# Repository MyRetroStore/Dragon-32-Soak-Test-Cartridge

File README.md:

# Dragon 32 Soak Test Cartridge

From the description on [WorldOfDragon](https://archive.worldofdragon.org/index.php?title=Dragon_32_Soak_Test)

_A cartridge designed to test the Dragon 32 hardware in a loop.
The ROM program will change a pattern on screen and lit a green led on the cartridge if tests are passing, and freeze the machine and lit a red led if any test fails.
The cartridge will not work on a Dragon 64 or a Dragon 200 as it performs a ROM checksum and later models will make the checksum test fail._

There is not much documentation on the Soak Test Cartridge for the Dragon 32 computer. 

After finding a photo of the PCB on WorldOfDragon I decided to reverse engineer the PCB 
and with the help of the community on the forums as well as a Dragon 32 Facebook group, I've managed to re-create the schematic and a replica PCB.

## Folders
Hardware - Schematic, PCB layout and Gerbers created with [KiCad](https://www.kicad.org/) 7.0.10

ROM - Binary file from worldofdragon.org

Photos - Photos of the orignal and replica PCB as well as screenshots of the cartridge in action. 

## BOM

| Reference  | Component                           |
| ---------- | ----------------------------------- |
| C1	       | 10u Electrolytic Capacitor          |
| C2,C3      | 10n Ceramic Capacitor               |
| D1	       | Red 5mm LED                         |
| D2	       | Green 5mm LED                       |
| DC1-4	     | 100n Ceramic Capacitor (Decoupling) |
| IC1	       | 74LS04                              |
| IC2	       | LM555                               |
| IC3	       | EPROM 27C64                         |
| IC4	       | 74LS10                              |
| R1-2, R5-8 | 3k3 Resistor 0.25W                  |
| R3         | 100k Resistor 0.25W                 |
| R4	       | 1k Resistor 0.25W                   |
| TR1,TR2    | BC237 Transistor                    |

I've tested the PCB in my Dragon 32 and it seems to work as expected, however I do not take any responsibility if you are building this and there is damage done to your Dragon 32 due to incorrect assembly or it doesn't work as expected. 

While this should be as close as possible a 100% replica to the orignal PCB there could be some error (Though hopefully not. Let me know if you find any) 

## Purchasing

If you don't want build this yourself the completed PCB can be purchased from:
- [MyRetroStore](https://myretrostore.co.uk/)
- [eBay](https://www.ebay.co.uk/str/myretrostoreuk)

## License
GNU General Public License v3.0

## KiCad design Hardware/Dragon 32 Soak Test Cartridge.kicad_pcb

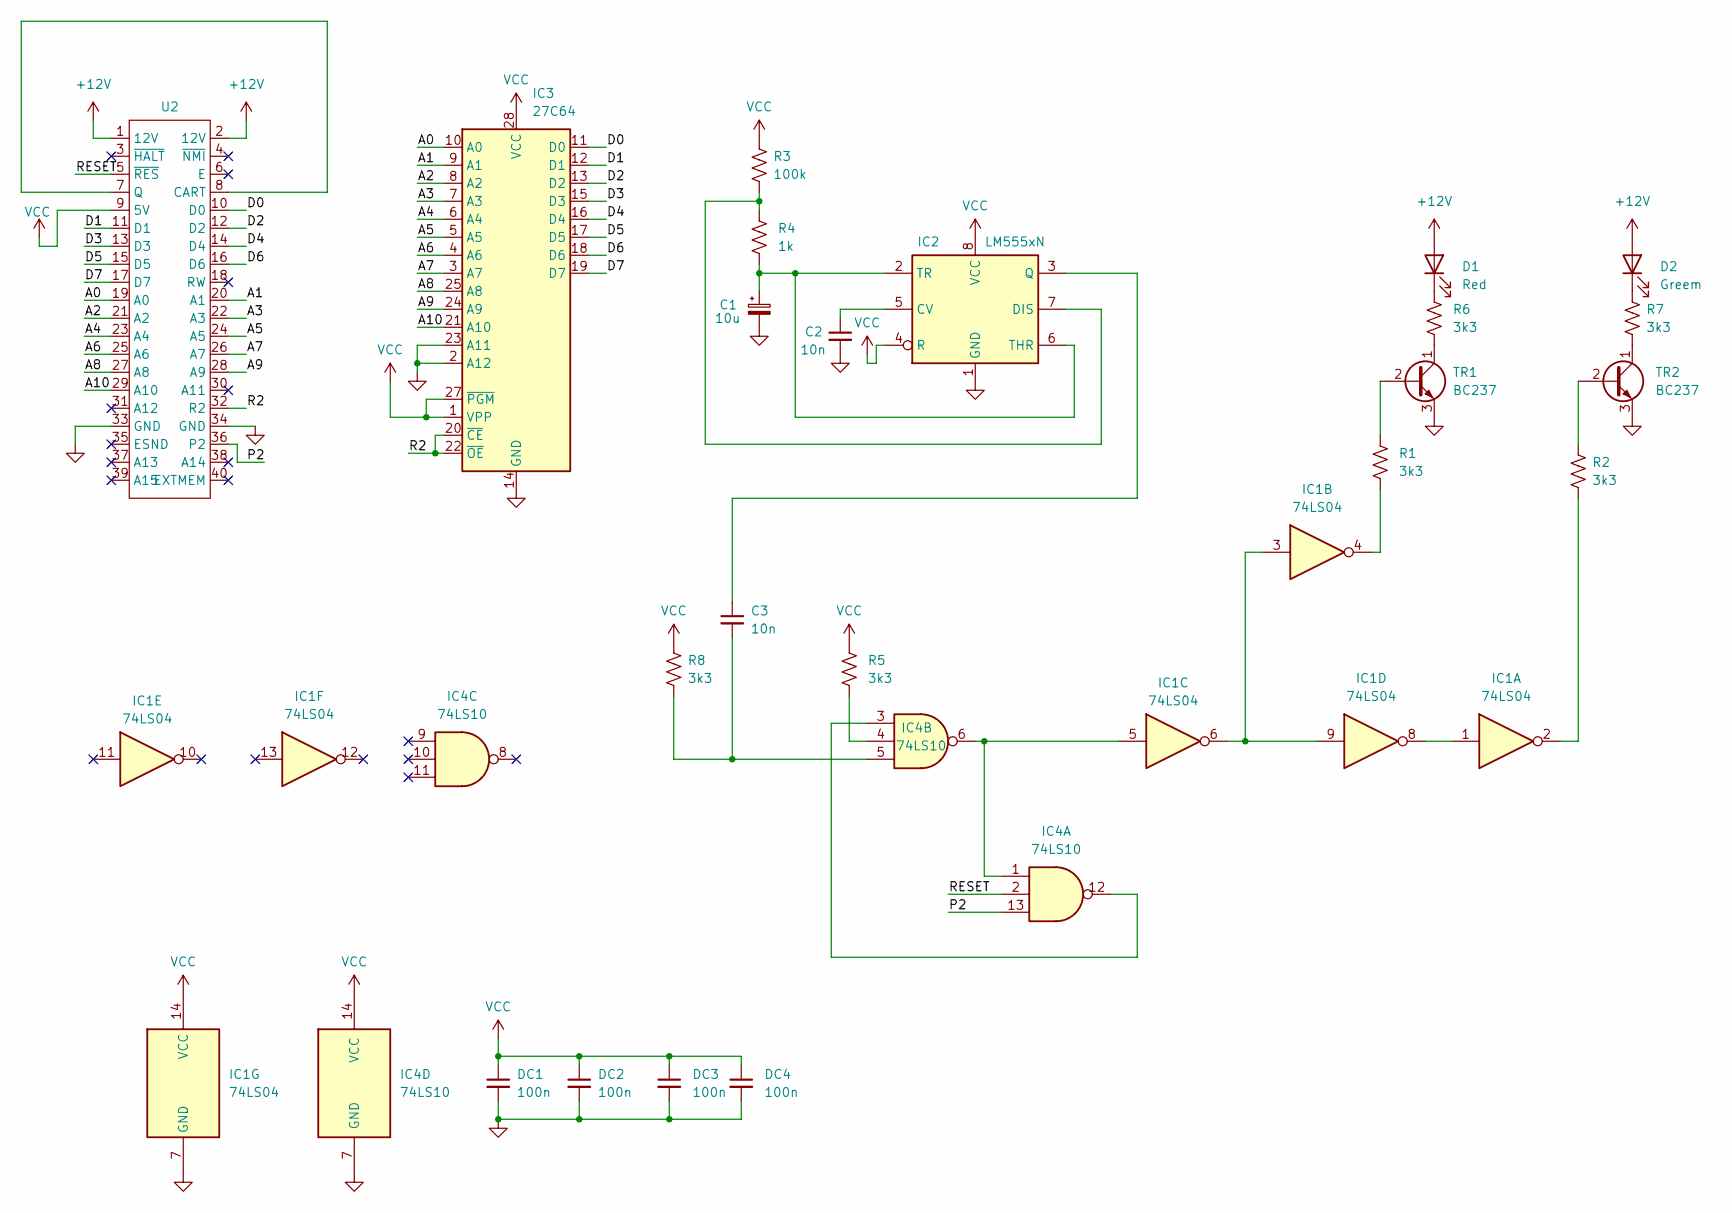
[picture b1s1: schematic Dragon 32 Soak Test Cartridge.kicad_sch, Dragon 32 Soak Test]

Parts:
C1: 10u; CP_Radial_D5.0mm_P2.50mm
C2, C3: 10n; C_Disc_D5.0mm_W2.5mm_P5.00mm
D1: Red; LED_D5.0mm
D2: Greem; LED_D5.0mm
DC1, DC2, DC3, DC4: 100n; C_Disc_D5.0mm_W2.5mm_P5.00mm
IC1: 74LS04; DIP-14_W7.62mm
IC2: LM555xN; DIP-8_W7.62mm
IC3: 27C64; DIP-28_W15.24mm
IC4: 74LS10; DIP-14_W7.62mm
R1, R2, R5, R6, R7, R8: 3k3; R_Axial_DIN0207_L6.3mm_D2.5mm_P10.16mm_Horizontal
R3: 100k; R_Axial_DIN0207_L6.3mm_D2.5mm_P10.16mm_Horizontal
R4: 1k; R_Axial_DIN0207_L6.3mm_D2.5mm_P10.16mm_Horizontal
TR1, TR2: BC237; TO-92
U2: Dragon 32

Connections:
+12V: D1.2 (A), D2.2 (A), U2.1 (12V), U2.2 (12V)
/A0: IC3.10 (A0), U2.19 (A0)
/A1: IC3.9 (A1), U2.20 (A1)
/A2: IC3.8 (A2), U2.21 (A2)
/A3: IC3.7 (A3), U2.22 (A3)
/A4: IC3.6 (A4), U2.23 (A4)
/A5: IC3.5 (A5), U2.24 (A5)
/A6: IC3.4 (A6), U2.25 (A6)
/A7: IC3.3 (A7), U2.26 (A7)
/A8: IC3.25 (A8), U2.27 (A8)
/A9: IC3.24 (A9), U2.28 (A9)
/A10: IC3.21 (A10), U2.29 (A10)
/D0: IC3.11 (D0), U2.10 (D0)
/D1: IC3.12 (D1), U2.11 (D1)
/D2: IC3.13 (D2), U2.12 (D2)
/D3: IC3.15 (D3), U2.13 (D3)
/D4: IC3.16 (D4), U2.14 (D4)
/D5: IC3.17 (D5), U2.15 (D5)
/D6: IC3.18 (D6), U2.16 (D6)
/D7: IC3.19 (D7), U2.17 (D7)
/P2: IC4.13, U2.36 (P2)
/R2: IC3.20 (~CE), IC3.22 (~OE), U2.32 (R2)
/RESET: IC4.2, U2.5 (~RES)
GND: C1.2, C2.2, DC1.2, DC2.2, DC3.2, DC4.2, IC1.7 (GND), IC2.1 (GND), IC3.2 (A12), IC3.14 (GND), IC3.23 (A11), IC4.7 (GND), TR1.3 (E), TR2.3 (E), U2.33 (GND), U2.34 (GND)
unnamed: C3.2, IC4.5, R8.1
unnamed: D1.1 (K), R6.1
unnamed: D2.1 (K), R7.1
unnamed: IC1.1, IC1.8
unnamed: IC1.2, R2.2
unnamed: IC1.3, IC1.6, IC1.9
unnamed: IC1.4, R1.2
unnamed: IC1.5, IC4.1, IC4.6
unnamed: C2.1, IC2.5 (CV)
unnamed: IC2.7 (DIS), R3.1, R4.1
unnamed: C3.1, IC2.3 (Q)
unnamed: C1.1, IC2.2 (TR), IC2.6 (THR), R4.2
unnamed: IC4.4, R5.2
unnamed: IC4.3, IC4.12
unnamed: R1.1, TR1.2 (B)
unnamed: R6.2, TR1.1 (C)
unnamed: R2.1, TR2.2 (B)
unnamed: R7.2, TR2.1 (C)
unnamed: U2.7 (Q), U2.8 (CART)
VCC: DC1.1, DC2.1, DC3.1, DC4.1, IC1.14 (VCC), IC2.4 (R), IC2.8 (VCC), IC3.1 (VPP), IC3.27 (~PGM), IC3.28 (VCC), IC4.14 (VCC), R3.2, R5.1, R8.2, U2.9 (5V)

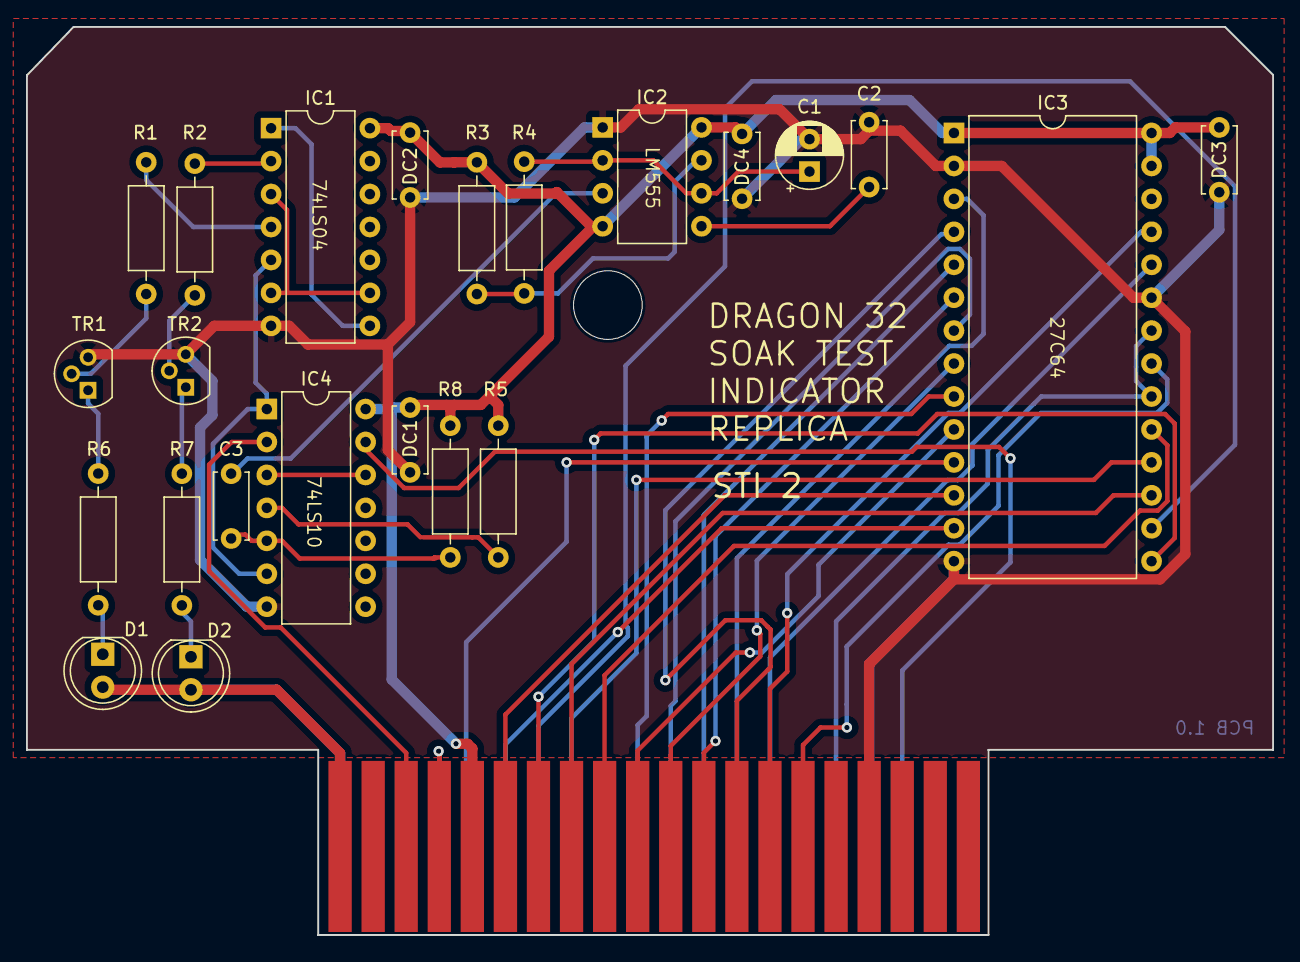
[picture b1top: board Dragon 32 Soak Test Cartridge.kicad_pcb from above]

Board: 2 copper layers, 96.1 x 70.0 mm, 24 parts (0 on the bottom side), 44 nets.

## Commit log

2024-01-28 Added BOM
2024-01-28 Updated BOM layout
